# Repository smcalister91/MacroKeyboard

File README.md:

# MacroKeyboard
This is a small macro keyboard made with Arduino and including a few different 3d printable case options.

Logic board was created with KiCAD. 

The cases are angled at 7.5 degrees to match the standard angle of a keyboard.

The logic board must be installed into the case before the switches are soldered in.

<h2>Component List:</h2>
<Table>
  <tr><td>  QTY  </td><td> ITEM  </td></tr>
  <tr><td>  1  </td><td>  Arduino Pro Micro  </td></tr>
  <tr><td>  4  </td><td>  M1.4 5-millimeter screws  </td></tr>
  <tr><td>  8  </td><td>  Cherry MX-compatible keyswitches  </td></tr>
  <tr><td>  8  </td><td>  Cherry MX-compatible keycaps  </td></tr>
  <tr><td>  8  </td><td>  10k ohm through-hole resistor  </td></tr>
  
</Table>

<h2>Folder Structure:</h2>

**Case3DModels:** Includes the STL files required to 3D print the two case options.

**Code:** Includes the Arduino code required to flash the firmware.

**KicadProjectFiles:** All files required by KiCAD to open the logic board files. Can be used to generate gerbers for sending to fab house.

**Pics:** A few pictures of the project and included assets.

<h2>Horizontal Case:</h2>

Designed to be placed behind the keyboard

<h2>Vertical Case:</h2>

Designed to be placed to the right or left of the keyboard

<h2>Logic Board:</h2>

<h2>Acknowledgements</h2>

Uses Nicohood's HID-project

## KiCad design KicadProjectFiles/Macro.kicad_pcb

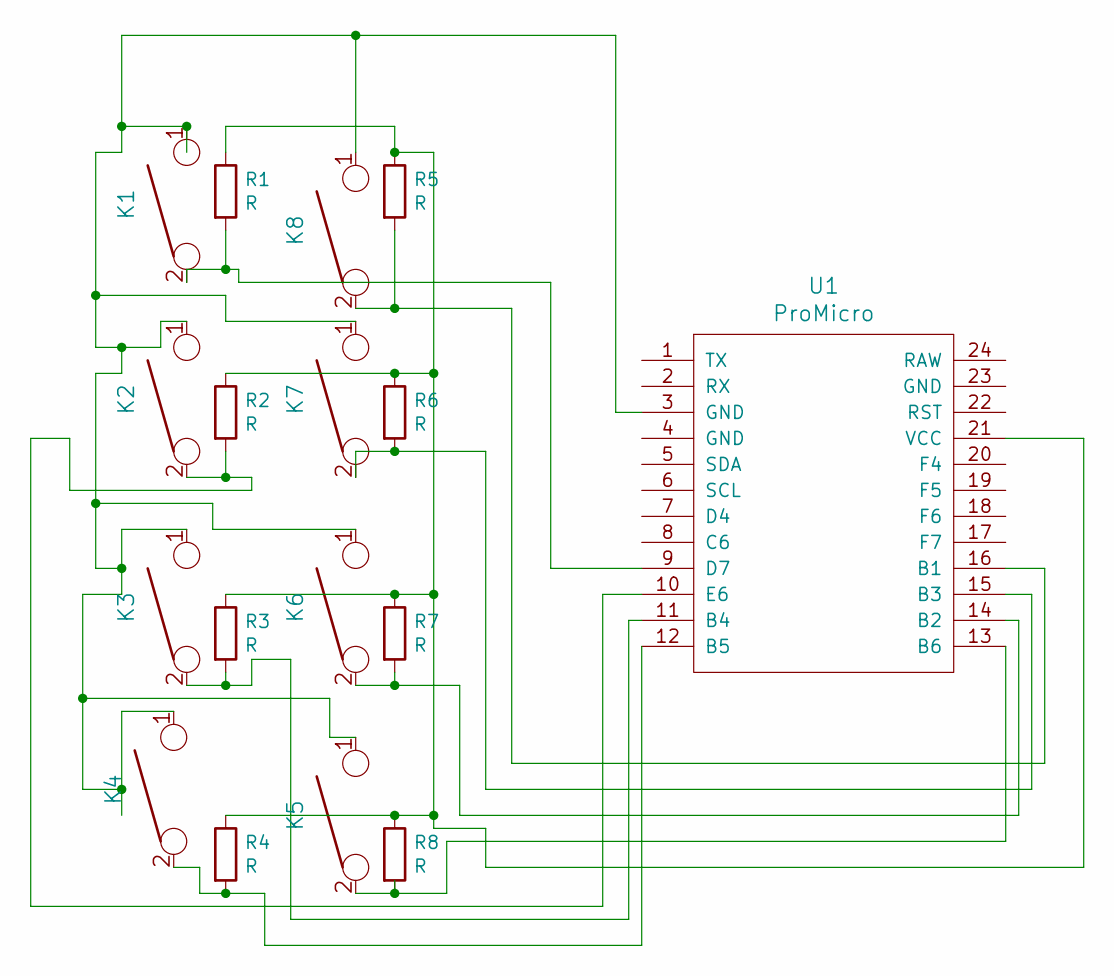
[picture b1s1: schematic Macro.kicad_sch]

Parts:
K1, K2, K3, K4, K5, K6, K7, K8: keyboard_parts_KEYSW; SW_Cherry_MX_1.00u_PCB
R1, R2, R3, R4, R5, R6, R7, R8: R; R_Axial_DIN0204_L3.6mm_D1.6mm_P5.08mm_Horizontal
U1: ProMicro

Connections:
unnamed: K1.1, K2.1, K3.1, K4.1, K5.1, K6.1, K7.1, K8.1, U1.3 (GND)
unnamed: K1.2, R1.2, U1.9 (D7)
unnamed: K2.2, R2.2, U1.10 (E6)
unnamed: K3.2, R3.2, U1.11 (B4)
unnamed: K4.2, R4.2, U1.12 (B5)
unnamed: K5.2, R8.2, U1.13 (B6)
unnamed: K6.2, R7.2, U1.14 (B2)
unnamed: K7.2, R6.2, U1.15 (B3)
unnamed: K8.2, R5.2, U1.16 (B1)
unnamed: R1.1, R2.1, R3.1, R4.1, R5.1, R6.1, R7.1, R8.1, U1.21 (VCC)

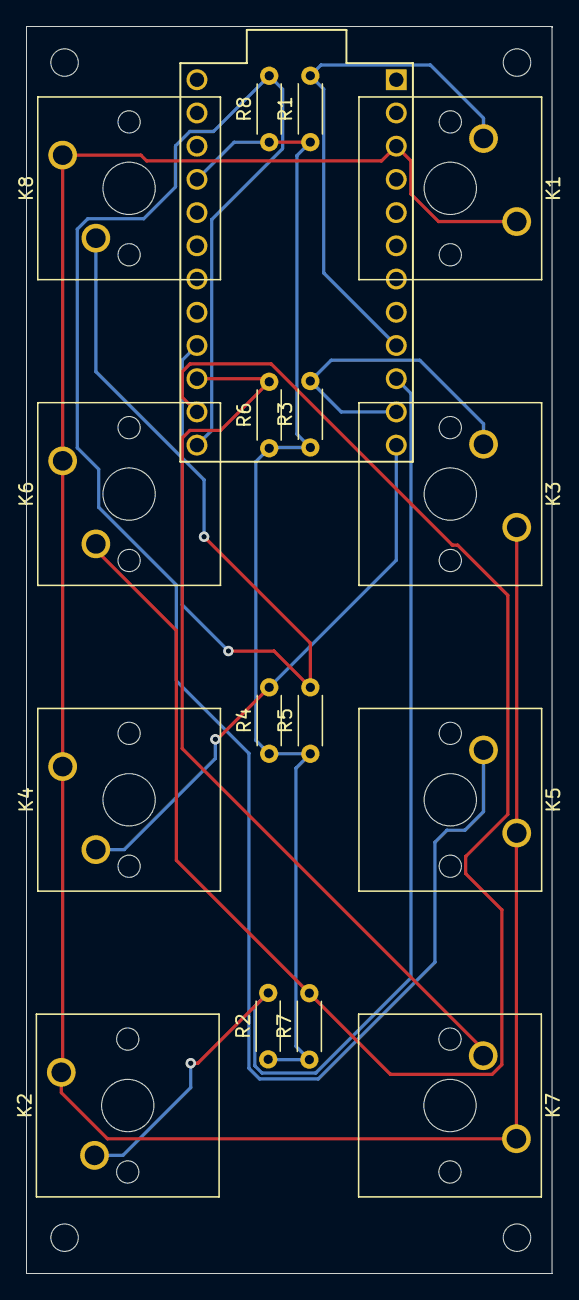
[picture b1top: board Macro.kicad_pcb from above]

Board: 2 copper layers, 40.2 x 95.4 mm, 17 parts (1 on the bottom side), 10 nets.
